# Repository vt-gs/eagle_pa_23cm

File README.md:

# eagle_pa_23cm
23cm (1265/1296 MHz) Power Amplifier EagleCAD files

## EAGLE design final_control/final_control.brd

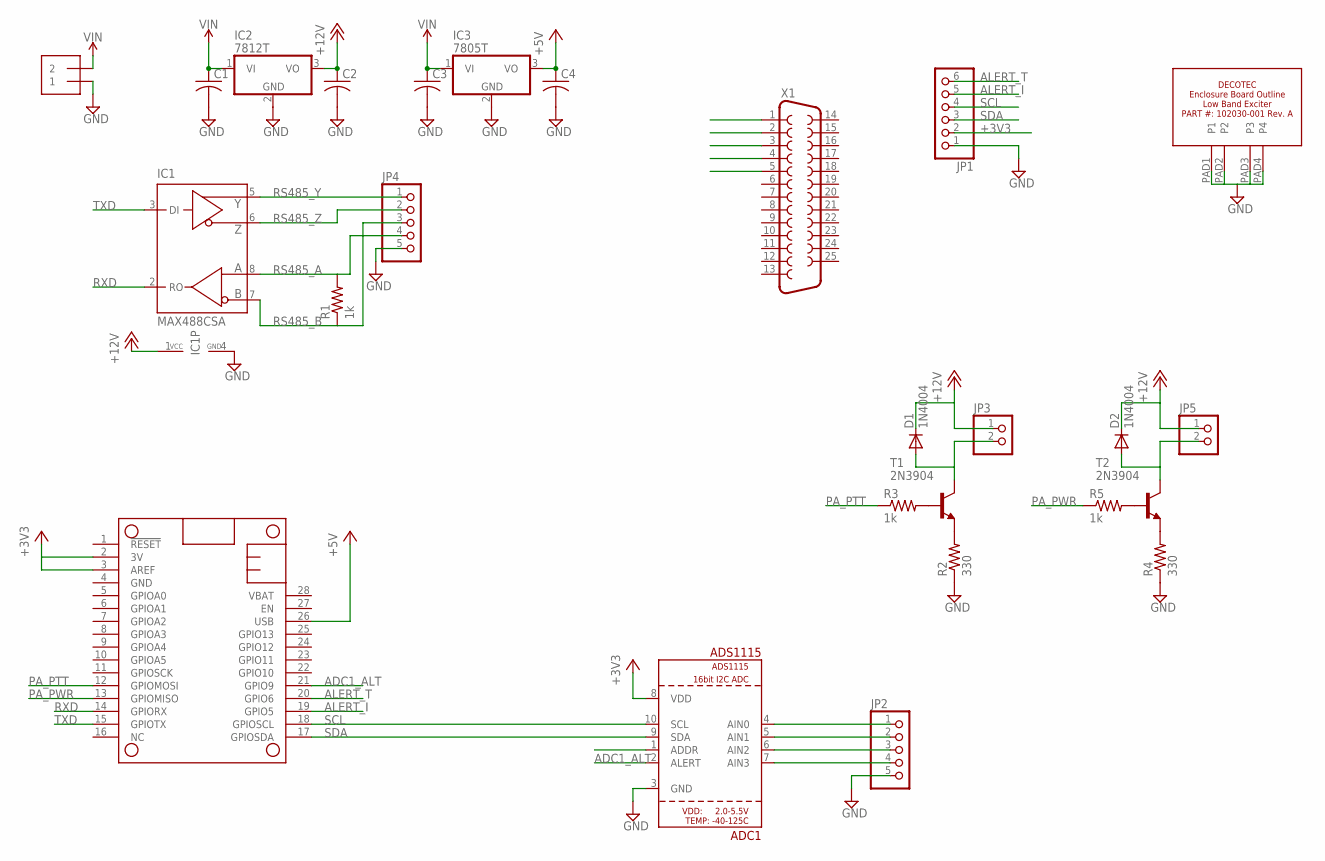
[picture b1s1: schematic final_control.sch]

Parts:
ADC1: ADS1115; MSOP10
C1, C2, C3, C4: C-USC1206K; C1206K
D1, D2: 1N4004; DO41-10
FEATHER_32U4: FEATHERWING_NODIM; FEATHERWING_DIM
IC1: MAX488CSA; SO08
IC2: 7812T; TO220H
IC3: 7805T; TO220H
J1: 1X2-3.5MM
JP1: PINHD-1X6; 1X06
JP2, JP4: PINHD-1X5; 1X05
JP3, JP5: PINHD-1X2; 1X02
R1, R3, R5: 1k; R0805
R2, R4: 330; R0805
T1, T2: 2N3904; TO92
U$2: DECOTEC_102030-001A
X1: DB25_FEMALEV; F25V

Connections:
+3V3: ADC1.8 (VDD), FEATHER_32U4.2 (3V), FEATHER_32U4.3 (AREF), JP1.2
+5V: C4.1, FEATHER_32U4.26 (USB), IC3.3 (VO)
+12V: C2.1, D1.C, D2.C, IC1.1 (VCC), IC2.3 (VO), JP3.1, JP5.1
ADC1_ALT: ADC1.2 (ALERT), FEATHER_32U4.21 (GPIO9)
ALERT_I: FEATHER_32U4.19 (GPIO5), JP1.5
ALERT_T: FEATHER_32U4.20 (GPIO6), JP1.6
GND: ADC1.3 (GND), C1.2, C2.2, C3.2, C4.2, FEATHER_32U4.4 (GND), IC1.4 (GND), IC2.2 (GND), IC3.2 (GND), J1.1, JP1.1, JP2.5, JP4.5, R2.1, R4.1, U$2.PAD1 (P1), U$2.PAD2 (P2), U$2.PAD3 (P3), U$2.PAD4 (P4)
unnamed: D2.A, JP5.2, T2.1 (C)
unnamed: R4.2, T2.3 (E)
unnamed: R5.2, T2.2 (B)
unnamed: ADC1.4 (AIN0), JP2.1
unnamed: ADC1.5 (AIN1), JP2.2
unnamed: ADC1.6 (AIN2), JP2.3
unnamed: ADC1.7 (AIN3), JP2.4
unnamed: D1.A, JP3.2, T1.1 (C)
unnamed: R2.2, T1.3 (E)
unnamed: R3.2, T1.2 (B)
PA_PTT: FEATHER_32U4.12 (GPIOMOSI), R3.1
PA_PWR: FEATHER_32U4.13 (GPIOMISO), R5.1
RS485_A: IC1.8 (A), JP4.4, R1.2
RS485_B: IC1.7 (B), JP4.3, R1.1
RS485_Y: IC1.5 (Y), JP4.1
RS485_Z: IC1.6 (Z), JP4.2
RXD: FEATHER_32U4.14 (GPIORX), IC1.2 (RO)
SCL: ADC1.10 (SCL), FEATHER_32U4.18 (GPIOSCL), JP1.4
SDA: ADC1.9 (SDA), FEATHER_32U4.17 (GPIOSDA), JP1.3
TXD: FEATHER_32U4.15 (GPIOTX), IC1.3 (DI)
VIN: C1.1, C3.1, IC2.1 (VI), IC3.1 (VI), J1.2

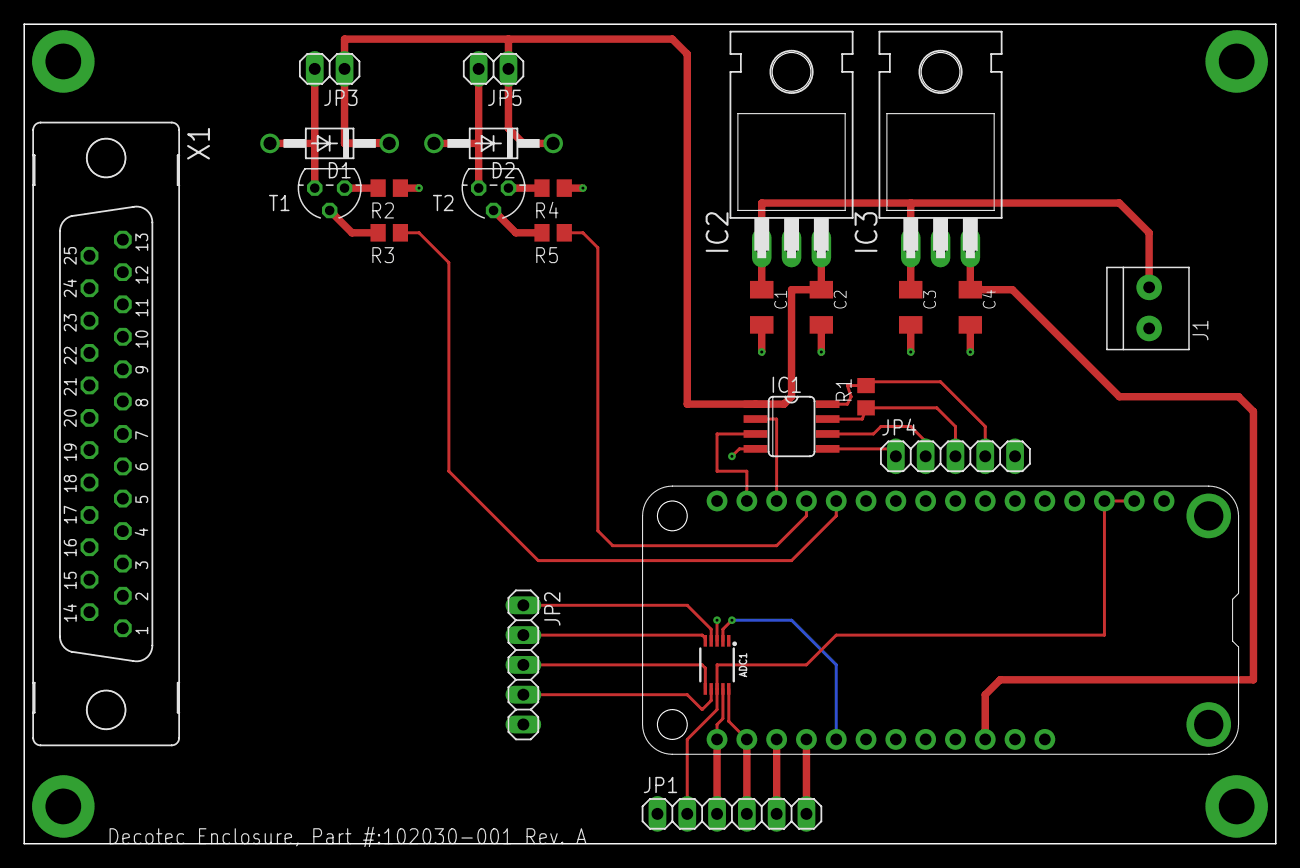
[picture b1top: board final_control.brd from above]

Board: 2 copper layers, 106.7 x 69.8 mm, 26 parts (0 on the bottom side), 28 nets.

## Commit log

2018-07-03 moving the 23cm pa eagle files into their own repo from the massive single 'eagle' repo.
2018-07-03 adding description for Eagle Control Panel
2018-07-03 updated eagle DESCRIPTION file

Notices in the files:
parts and their libraries:
SparkFun-Retired: Licensing: Creative Commons ShareAlike 4.0 International - https://creativecommons.org/licenses/by-sa/4.0
